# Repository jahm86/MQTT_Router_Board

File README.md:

# MQTT_Router_Board
Tarjeta electrónica para proyecto didáctico de router MQTT

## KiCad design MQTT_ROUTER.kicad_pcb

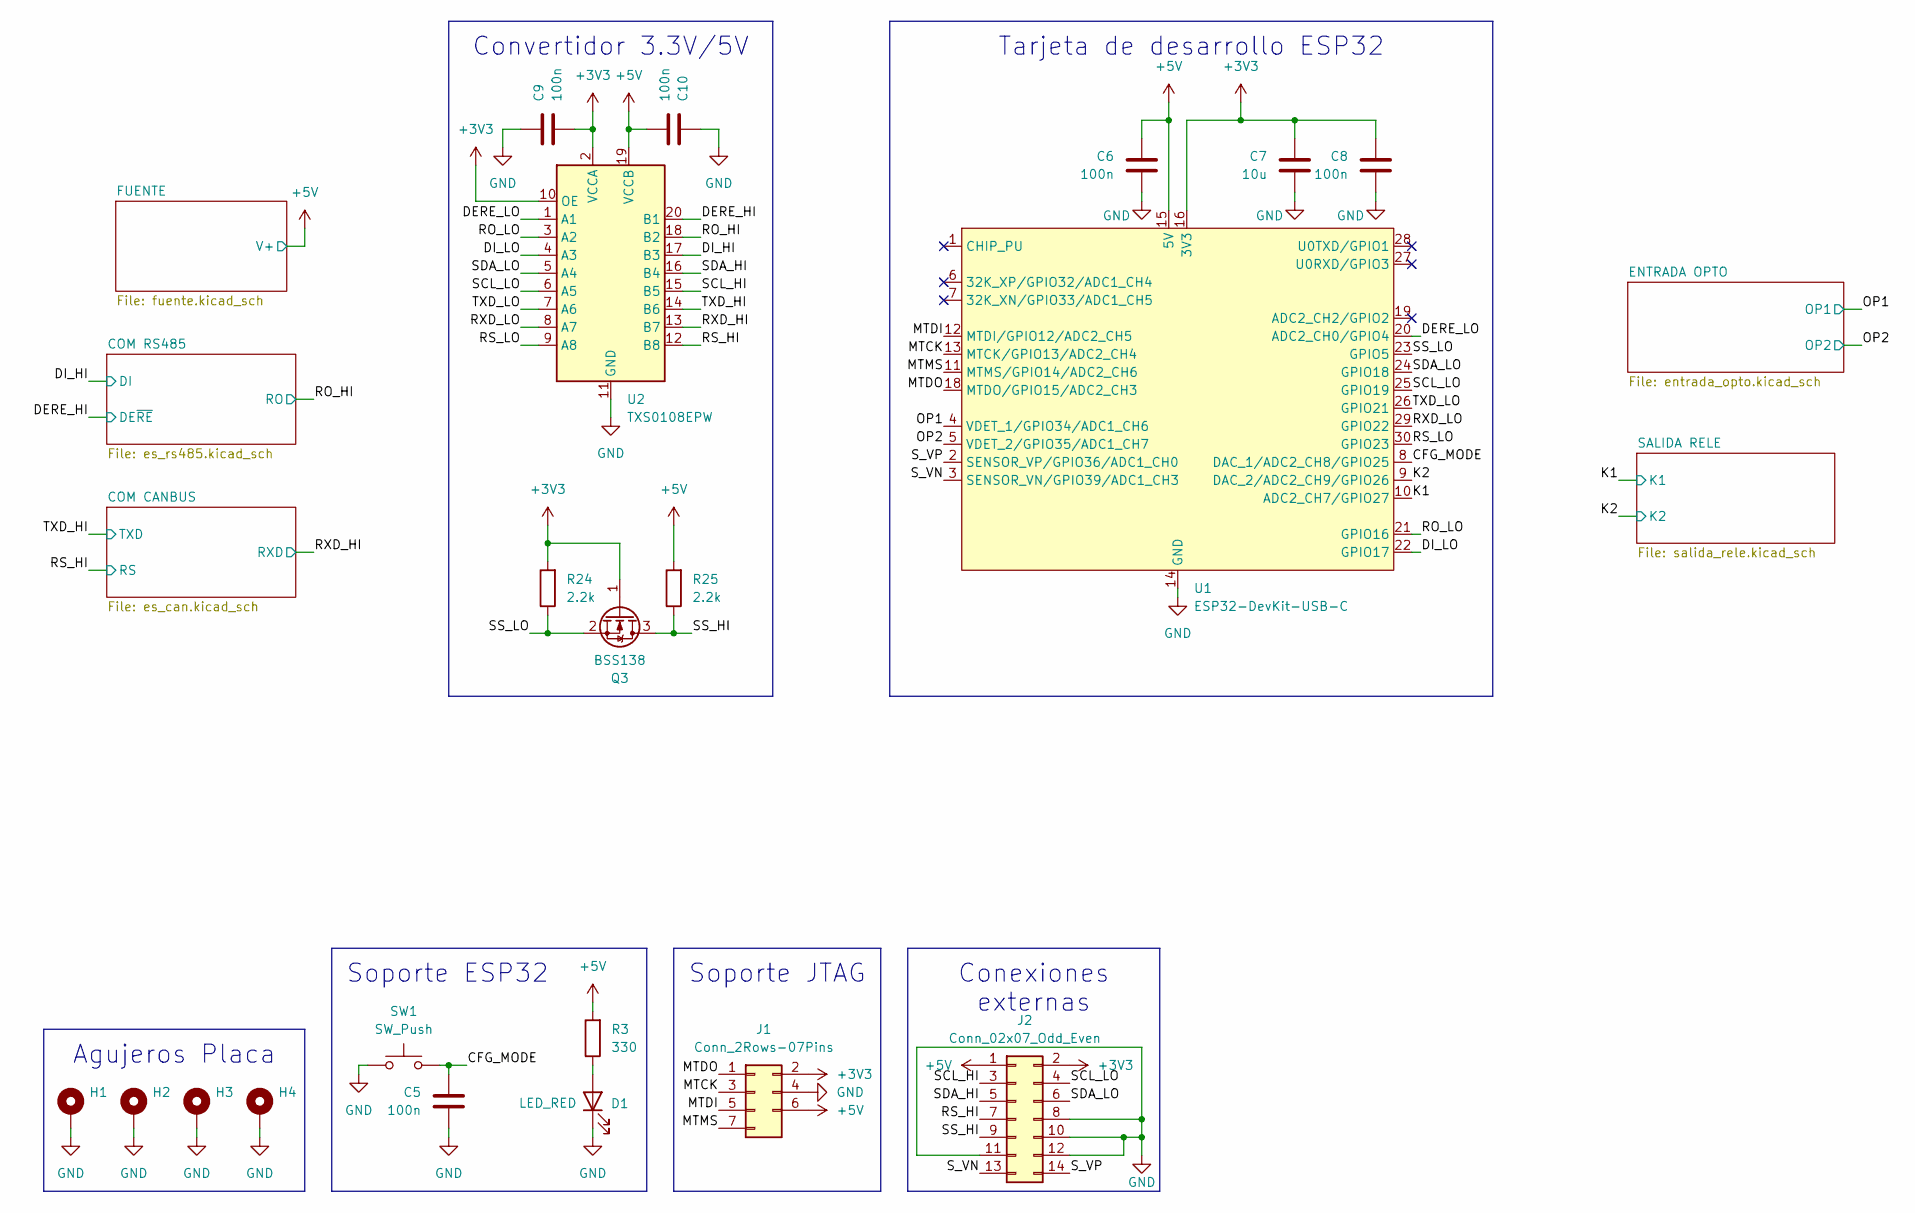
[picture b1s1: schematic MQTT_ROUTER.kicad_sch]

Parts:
C5, C6, C8, C9, C10: 100n; C_0805_2012Metric
C7: 10u; C_1206_3216Metric
D1: LED_RED; LED_D5.0mm
H1, H2, H3, H4: MountingHole_Pad; MountingHole_3.5mm_Pad_Via
J1: Conn_2Rows-07Pins; PinSocket_2x04_P2.54mm_Vertical
J2: Conn_02x07_Odd_Even; PinSocket_2x07_P2.54mm_Vertical
Q3: BSS138; SOT-23
R3: 330; R_0805_2012Metric
R24, R25: 2.2k; R_0805_2012Metric
SW1: SW_Push; SW_PUSH_6mm
U1: ESP32-DevKit-USB-C
U2: TXS0108EPW; TSSOP-20_4.4x6.5mm_P0.65mm

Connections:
+3V3: C7.1, C8.1, C9.2, J1.2, J2.2, Q3.1 (G), R24.2, U1.16 (3V3), U2.2 (VCCA), U2.10 (OE); also elsewhere on the board
+5V: C6.1, C10.2, J1.6, J2.1, R3.2, R25.2, U1.15 (5V), U2.19 (VCCB); also elsewhere on the board
/CFG_MODE: C5.1, SW1.2, U1.8 (DAC_1/ADC2_CH8/GPIO25)
/DERE_HI: U2.20 (B1); also elsewhere on the board
/DERE_LO: U1.20 (ADC2_CH0/GPIO4), U2.1 (A1)
/DI_HI: U2.17 (B3); also elsewhere on the board
/DI_LO: U1.22 (GPIO17), U2.4 (A3)
/K1: U1.10 (ADC2_CH7/GPIO27); also elsewhere on the board
/K2: U1.9 (DAC_2/ADC2_CH9/GPIO26); also elsewhere on the board
/MTCK: J1.3, U1.13 (MTCK/GPIO13/ADC2_CH4)
/MTDI: J1.5, U1.12 (MTDI/GPIO12/ADC2_CH5)
/MTDO: J1.1, U1.18 (MTDO/GPIO15/ADC2_CH3)
/MTMS: J1.7, U1.11 (MTMS/GPIO14/ADC2_CH6)
/OP1: U1.4 (VDET_1/GPIO34/ADC1_CH6); also elsewhere on the board
/OP2: U1.5 (VDET_2/GPIO35/ADC1_CH7); also elsewhere on the board
/RO_HI: U2.18 (B2); also elsewhere on the board
/RO_LO: U1.21 (GPIO16), U2.3 (A2)
/RS_HI: J2.7, U2.12 (B8); also elsewhere on the board
/RS_LO: U1.30 (GPIO23), U2.9 (A8)
/RXD_HI: U2.13 (B7); also elsewhere on the board
/RXD_LO: U1.29 (GPIO22), U2.8 (A7)
/SCL_HI: J2.3, U2.15 (B5)
/SCL_LO: J2.4, U1.25 (GPIO19), U2.6 (A5)
/SDA_HI: J2.5, U2.16 (B4)
/SDA_LO: J2.6, U1.24 (GPIO18), U2.5 (A4)
/SS_HI: J2.9, Q3.3 (D), R25.1
/SS_LO: Q3.2 (S), R24.1, U1.23 (GPIO5)
/S_VN: J2.13, U1.3 (SENSOR_VN/GPIO39/ADC1_CH3)
/S_VP: J2.14, U1.2 (SENSOR_VP/GPIO36/ADC1_CH0)
/TXD_HI: U2.14 (B6); also elsewhere on the board
/TXD_LO: U1.26 (GPIO21), U2.7 (A6)
GND: C5.2, C6.2, C7.2, C8.2, C9.1, C10.1, D1.1 (K), H1.1, H2.1, H3.1, H4.1, J1.4, J2.8, J2.10, J2.11, J2.12, SW1.1, U1.14 (GND), U1.17 (GND), U2.11 (GND); also elsewhere on the board
unnamed: D1.2 (A), R3.1

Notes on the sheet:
Soporte ESP32
Agujeros Placa
Convertidor 3.3V/5V
Tarjeta de desarrollo ESP32
Soporte JTAG
Conexiones externas

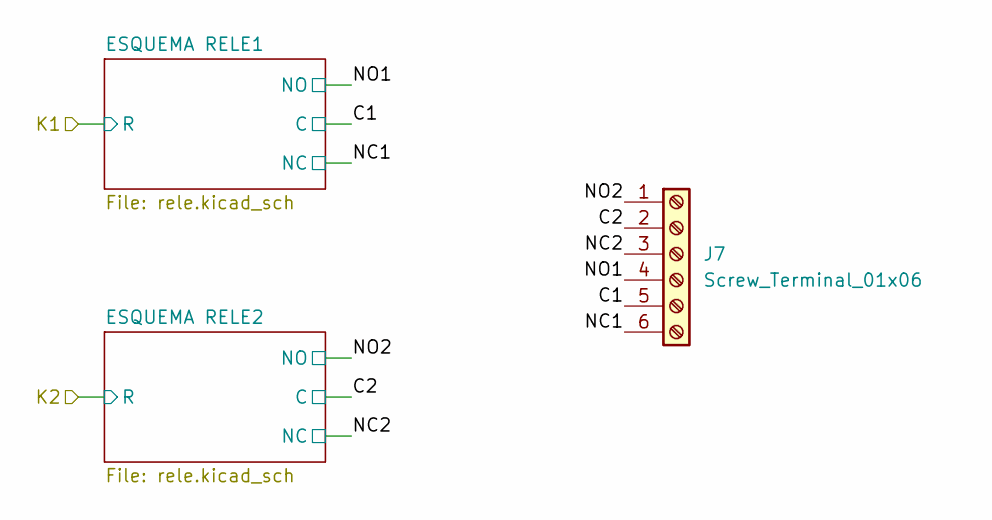
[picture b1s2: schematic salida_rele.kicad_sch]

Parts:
J7: Screw_Terminal_01x06; TerminalBlock_Phoenix_MKDS-1,5-6_1x06_P5.00mm_Horizontal

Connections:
/SALIDA RELE/C1: J7.5; also elsewhere on the board
/SALIDA RELE/C2: J7.2; also elsewhere on the board
/SALIDA RELE/NC1: J7.6; also elsewhere on the board
/SALIDA RELE/NC2: J7.3; also elsewhere on the board
/SALIDA RELE/NO1: J7.4; also elsewhere on the board
/SALIDA RELE/NO2: J7.1; also elsewhere on the board

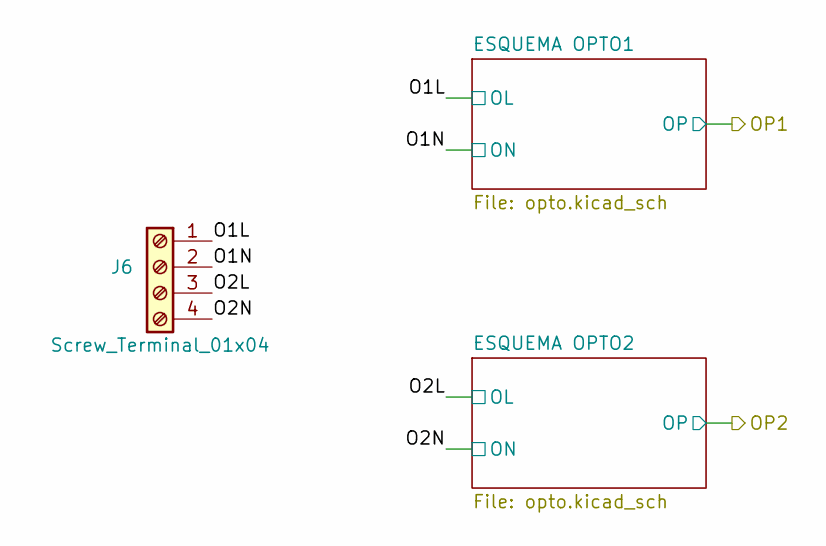
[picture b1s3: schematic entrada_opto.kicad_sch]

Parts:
J6: Screw_Terminal_01x04; TerminalBlock_Phoenix_MKDS-1,5-4_1x04_P5.00mm_Horizontal

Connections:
/ENTRADA OPTO/O1L: J6.1; also elsewhere on the board
/ENTRADA OPTO/O1N: J6.2; also elsewhere on the board
/ENTRADA OPTO/O2L: J6.3; also elsewhere on the board
/ENTRADA OPTO/O2N: J6.4; also elsewhere on the board

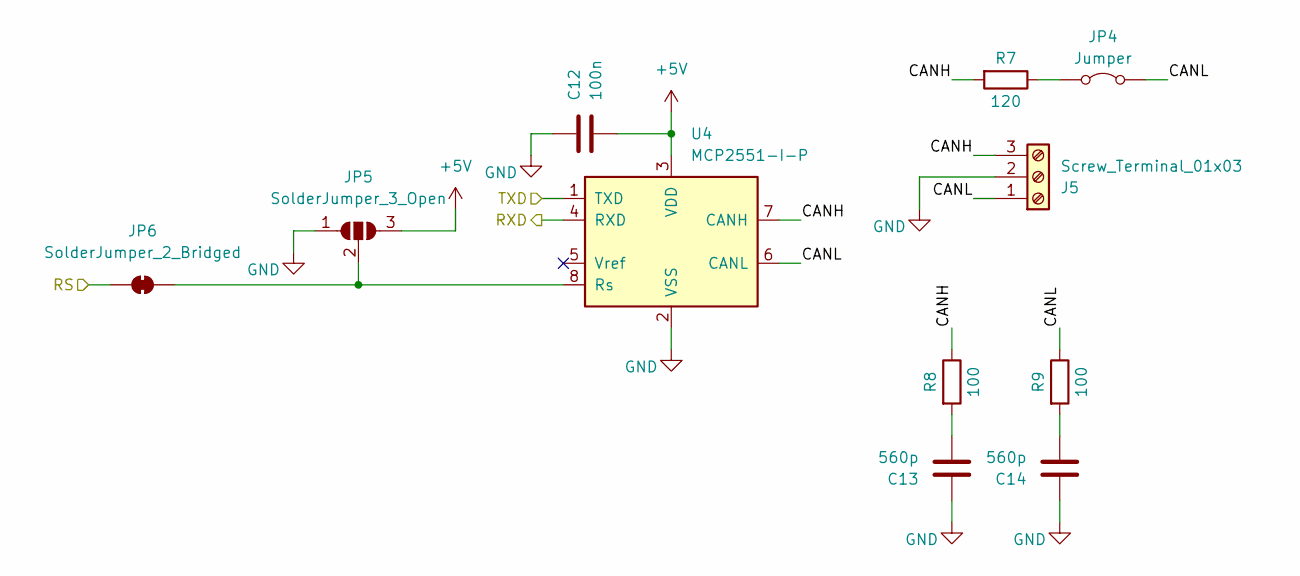
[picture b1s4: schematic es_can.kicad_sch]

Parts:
C12: 100n; C_0805_2012Metric
C13, C14: 560p; C_0805_2012Metric
J5: Screw_Terminal_01x03; TerminalBlock_Phoenix_MKDS-1,5-3_1x03_P5.00mm_Horizontal
JP4: Jumper; PinHeader_1x02_P2.54mm_Vertical
JP5: SolderJumper_3_Open; SolderJumper-3_P1.3mm_Open_RoundedPad1.0x1.5mm
JP6: SolderJumper_2_Bridged; SolderJumper-2_P1.3mm_Bridged_RoundedPad1.0x1.5mm
R7: 120; R_0805_2012Metric
R8, R9: 100; R_0805_2012Metric
U4: MCP2551-I-P; DIP-8_W7.62mm

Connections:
+5V: C12.2, JP5.3 (B), U4.3 (VDD); also elsewhere on the board
/COM CANBUS/CANH: J5.3, R7.2, R8.1, U4.7 (CANH)
/COM CANBUS/CANL: J5.1, JP4.2 (B), R9.1, U4.6 (CANL)
/RS_HI: JP6.1 (A); also elsewhere on the board
/RXD_HI: U4.4 (RXD); also elsewhere on the board
/TXD_HI: U4.1 (TXD); also elsewhere on the board
GND: C12.1, C13.1, C14.1, J5.2, JP5.1 (A), U4.2 (VSS); also elsewhere on the board
unnamed: C13.2, R8.2
unnamed: C14.2, R9.2
unnamed: JP4.1 (A), R7.1
unnamed: JP5.2 (C), JP6.2 (B), U4.8 (Rs)

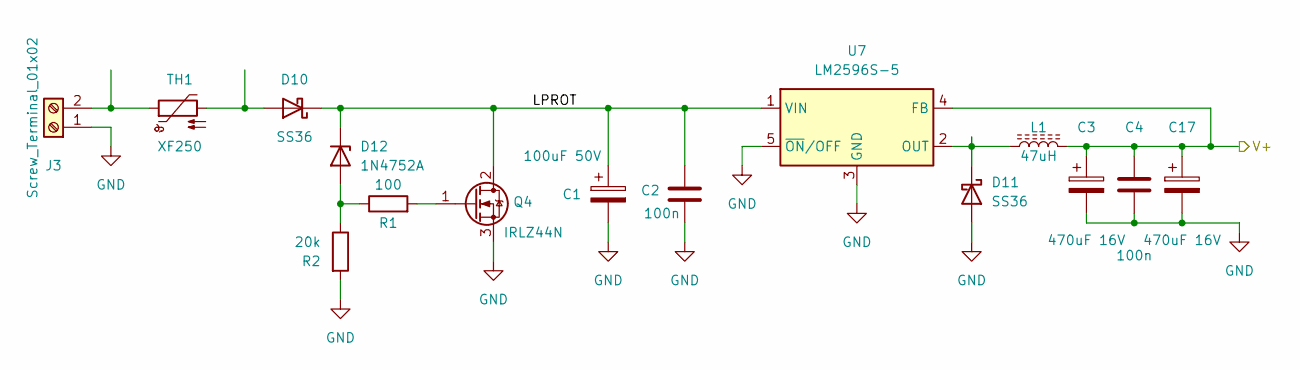
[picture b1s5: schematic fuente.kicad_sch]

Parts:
C1: 100uF 50V; CP_Radial_D10.0mm_P5.00mm
C2, C4: 100n; C_0805_2012Metric
C3, C17: 470uF 16V; CP_Radial_D10.0mm_P5.00mm
D10, D11: SS36; D_SMC
D12: 1N4752A; D_DO-41_SOD81_P10.16mm_Horizontal
J3: Screw_Terminal_01x02; TerminalBlock_Phoenix_MKDS-1,5-2_1x02_P5.00mm_Horizontal
L1: 47uH; L_Bourns_SRR1260
Q4: IRLZ44N; TO-220-3_Horizontal_TabDown
R1: 100; R_0805_2012Metric
R2: 20k; R_0805_2012Metric
TH1: XF250; Fuse_BelFuse_0ZRE0125FF_L21.2mm_W5.3mm
U7: LM2596S-5; TO-263-5_TabPin3

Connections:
+5V: C3.1, C4.1, C17.1, L1.2, U7.4 (FB); also elsewhere on the board
/FUENTE/LPROT: C1.1, C2.1, D10.1 (K), D12.1 (K), Q4.2 (D), U7.1 (VIN)
GND: C1.2, C2.2, C3.2, C4.2, C17.2, D11.2 (A), J3.1, Q4.3 (S), R2.2, U7.3 (GND), U7.5 (~ON/OFF); also elsewhere on the board
unnamed: D10.2 (A), TH1.2
unnamed: D11.1 (K), L1.1, U7.2 (OUT)
unnamed: D12.2 (A), R1.1, R2.1
unnamed: J3.2, TH1.1
unnamed: Q4.1 (G), R1.2

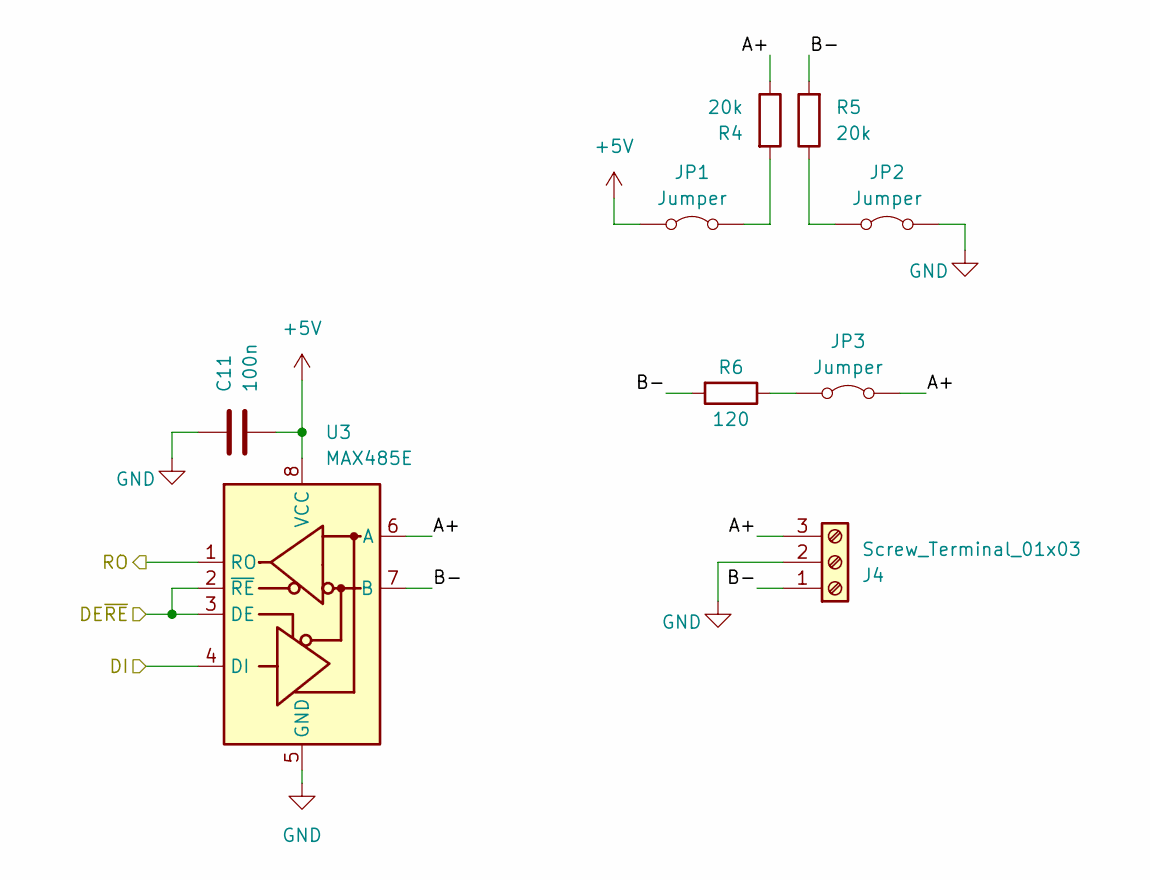
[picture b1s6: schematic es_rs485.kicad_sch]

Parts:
C11: 100n; C_0805_2012Metric
J4: Screw_Terminal_01x03; TerminalBlock_Phoenix_MKDS-1,5-3_1x03_P5.00mm_Horizontal
JP1, JP2, JP3: Jumper; PinHeader_1x02_P2.54mm_Vertical
R4, R5: 20k; R_0805_2012Metric
R6: 120; R_0805_2012Metric
U3: MAX485E; SOIC-8_3.9x4.9mm_P1.27mm

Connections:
+5V: C11.2, JP1.1 (A), U3.8 (VCC); also elsewhere on the board
/COM RS485/A+: J4.3, JP3.2 (B), R4.1, U3.6 (A)
/COM RS485/B-: J4.1, R5.2, R6.2, U3.7 (B)
/DERE_HI: U3.2 (~RE), U3.3 (DE); also elsewhere on the board
/DI_HI: U3.4 (DI); also elsewhere on the board
/RO_HI: U3.1 (RO); also elsewhere on the board
GND: C11.1, J4.2, JP2.1 (A), U3.5 (GND); also elsewhere on the board
unnamed: JP1.2 (B), R4.2
unnamed: JP2.2 (B), R5.1
unnamed: JP3.1 (A), R6.1

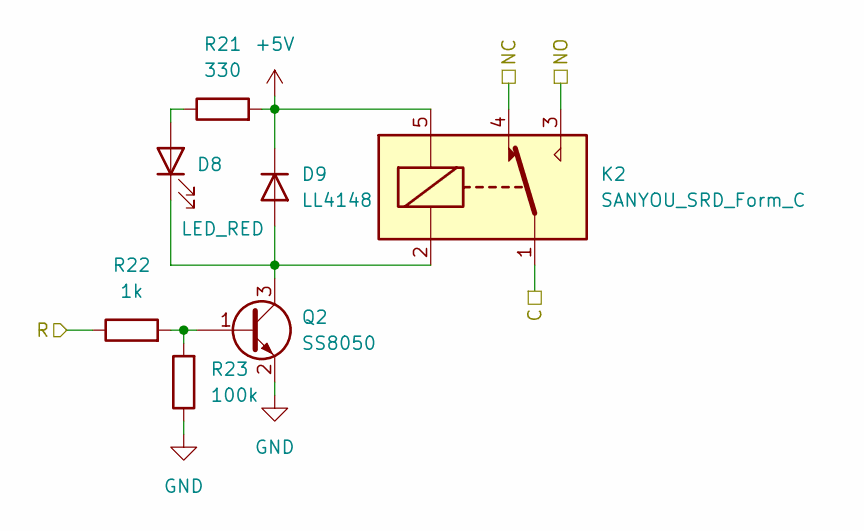
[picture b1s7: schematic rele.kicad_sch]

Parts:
D8: LED_RED; LED_D5.0mm
D9: LL4148; D_MiniMELF
K2: SANYOU_SRD_Form_C; Relay_SPDT_SANYOU_SRD_Series_Form_C
Q2: SS8050; SOT-23
R21: 330; R_0805_2012Metric
R22: 1k; R_0805_2012Metric
R23: 100k; R_0805_2012Metric

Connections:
+5V: D9.1 (K), K2.5, R21.2; also elsewhere on the board
/K2: R22.1; also elsewhere on the board
/SALIDA RELE/C2: K2.1; also elsewhere on the board
/SALIDA RELE/NC2: K2.4; also elsewhere on the board
/SALIDA RELE/NO2: K2.3; also elsewhere on the board
GND: Q2.2 (E), R23.1; also elsewhere on the board
unnamed: D8.2 (A), R21.1
unnamed: D8.1 (K), D9.2 (A), K2.2, Q2.3 (C)
unnamed: Q2.1 (B), R22.2, R23.2

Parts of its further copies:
D6: LED_RED; LED_D5.0mm
D7: LL4148; D_MiniMELF
K1: SANYOU_SRD_Form_C; Relay_SPDT_SANYOU_SRD_Series_Form_C
Q1: SS8050; SOT-23
R18: 330; R_0805_2012Metric
R19: 1k; R_0805_2012Metric
R20: 100k; R_0805_2012Metric

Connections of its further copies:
+5V: D7.1 (K), K1.5, R18.2; also elsewhere on the board
/K1: R19.1; also elsewhere on the board
/SALIDA RELE/C1: K1.1; also elsewhere on the board
/SALIDA RELE/NC1: K1.4; also elsewhere on the board
/SALIDA RELE/NO1: K1.3; also elsewhere on the board
GND: Q1.2 (E), R20.1; also elsewhere on the board
unnamed: D6.2 (A), R18.1
unnamed: D6.1 (K), D7.2 (A), K1.2, Q1.3 (C)
unnamed: Q1.1 (B), R19.2, R20.2

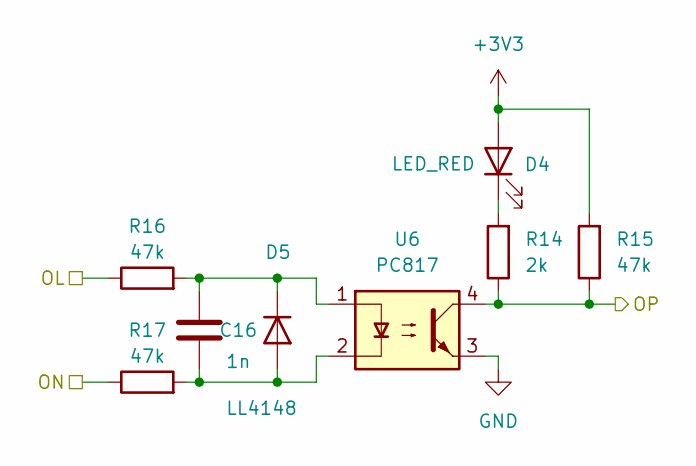
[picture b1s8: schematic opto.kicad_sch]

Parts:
C16: 1n; C_0805_2012Metric
D4: LED_RED; LED_D5.0mm
D5: LL4148; D_MiniMELF
R14: 2k; R_0805_2012Metric
R15: 47k; R_0805_2012Metric
R16, R17: 47k; R_1206_3216Metric
U6: PC817; DIP-4_W7.62mm

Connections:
+3V3: D4.2 (A), R15.2; also elsewhere on the board
/ENTRADA OPTO/O2L: R16.1; also elsewhere on the board
/ENTRADA OPTO/O2N: R17.1; also elsewhere on the board
/OP2: R14.1, R15.1, U6.4; also elsewhere on the board
GND: U6.3; also elsewhere on the board
unnamed: D4.1 (K), R14.2
unnamed: C16.2, D5.2 (A), R17.2, U6.2
unnamed: C16.1, D5.1 (K), R16.2, U6.1

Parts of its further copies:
C15: 1n; C_0805_2012Metric
D2: LED_RED; LED_D5.0mm
D3: LL4148; D_MiniMELF
R10: 2k; R_0805_2012Metric
R11: 47k; R_0805_2012Metric
R12, R13: 47k; R_1206_3216Metric
U5: PC817; DIP-4_W7.62mm

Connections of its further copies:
+3V3: D2.2 (A), R11.2; also elsewhere on the board
/ENTRADA OPTO/O1L: R12.1; also elsewhere on the board
/ENTRADA OPTO/O1N: R13.1; also elsewhere on the board
/OP1: R10.1, R11.1, U5.4; also elsewhere on the board
GND: U5.3; also elsewhere on the board
unnamed: D2.1 (K), R10.2
unnamed: C15.2, D3.2 (A), R13.2, U5.2
unnamed: C15.1, D3.1 (K), R12.2, U5.1

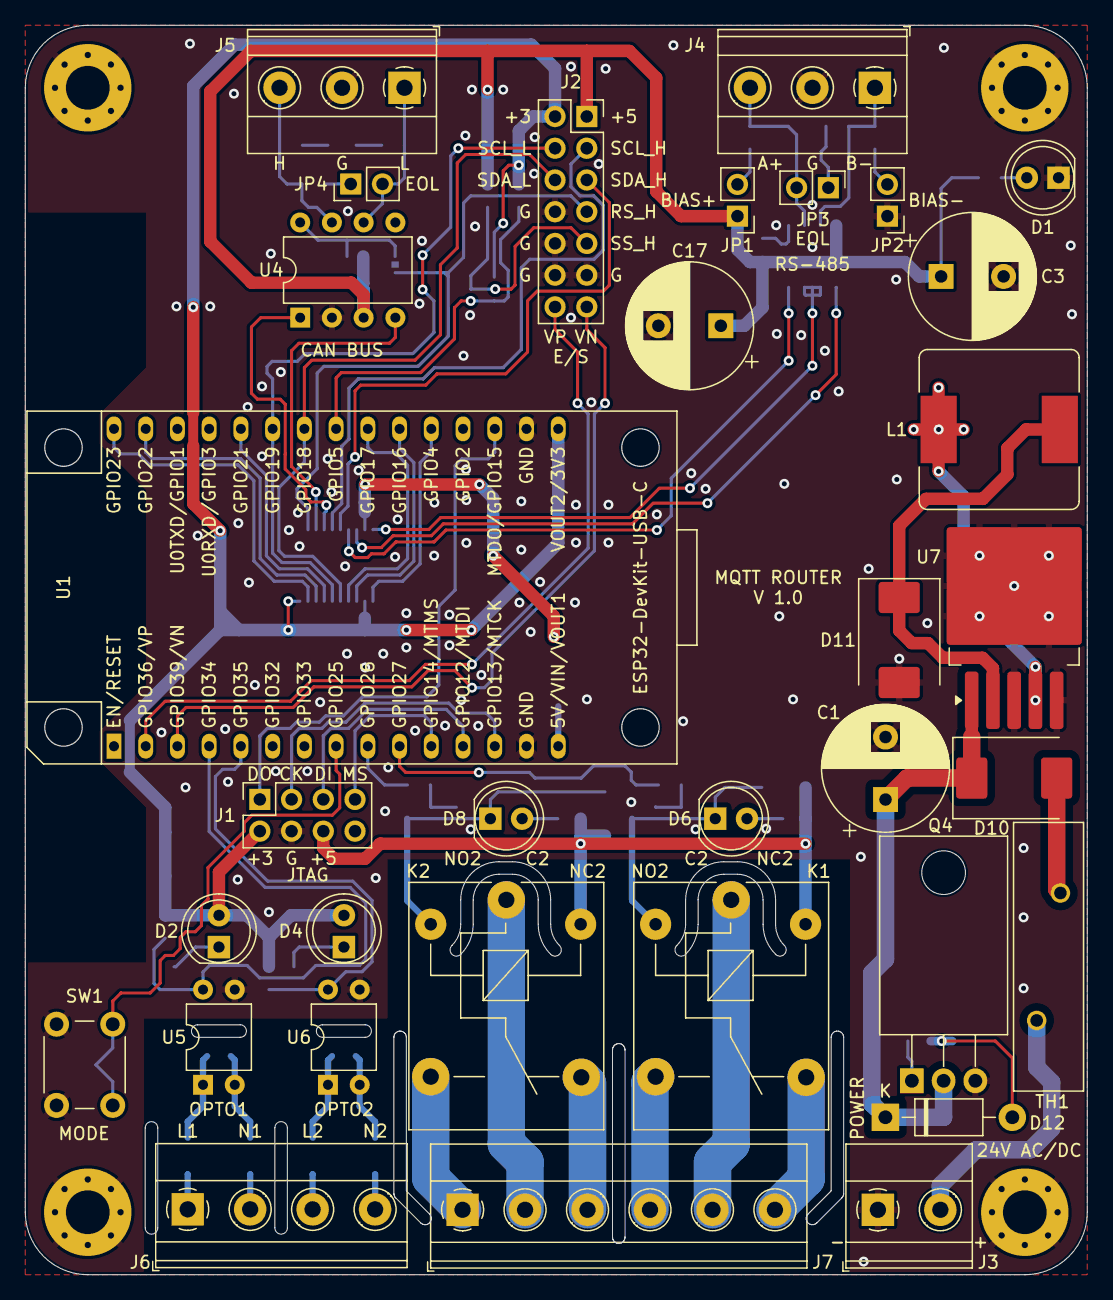
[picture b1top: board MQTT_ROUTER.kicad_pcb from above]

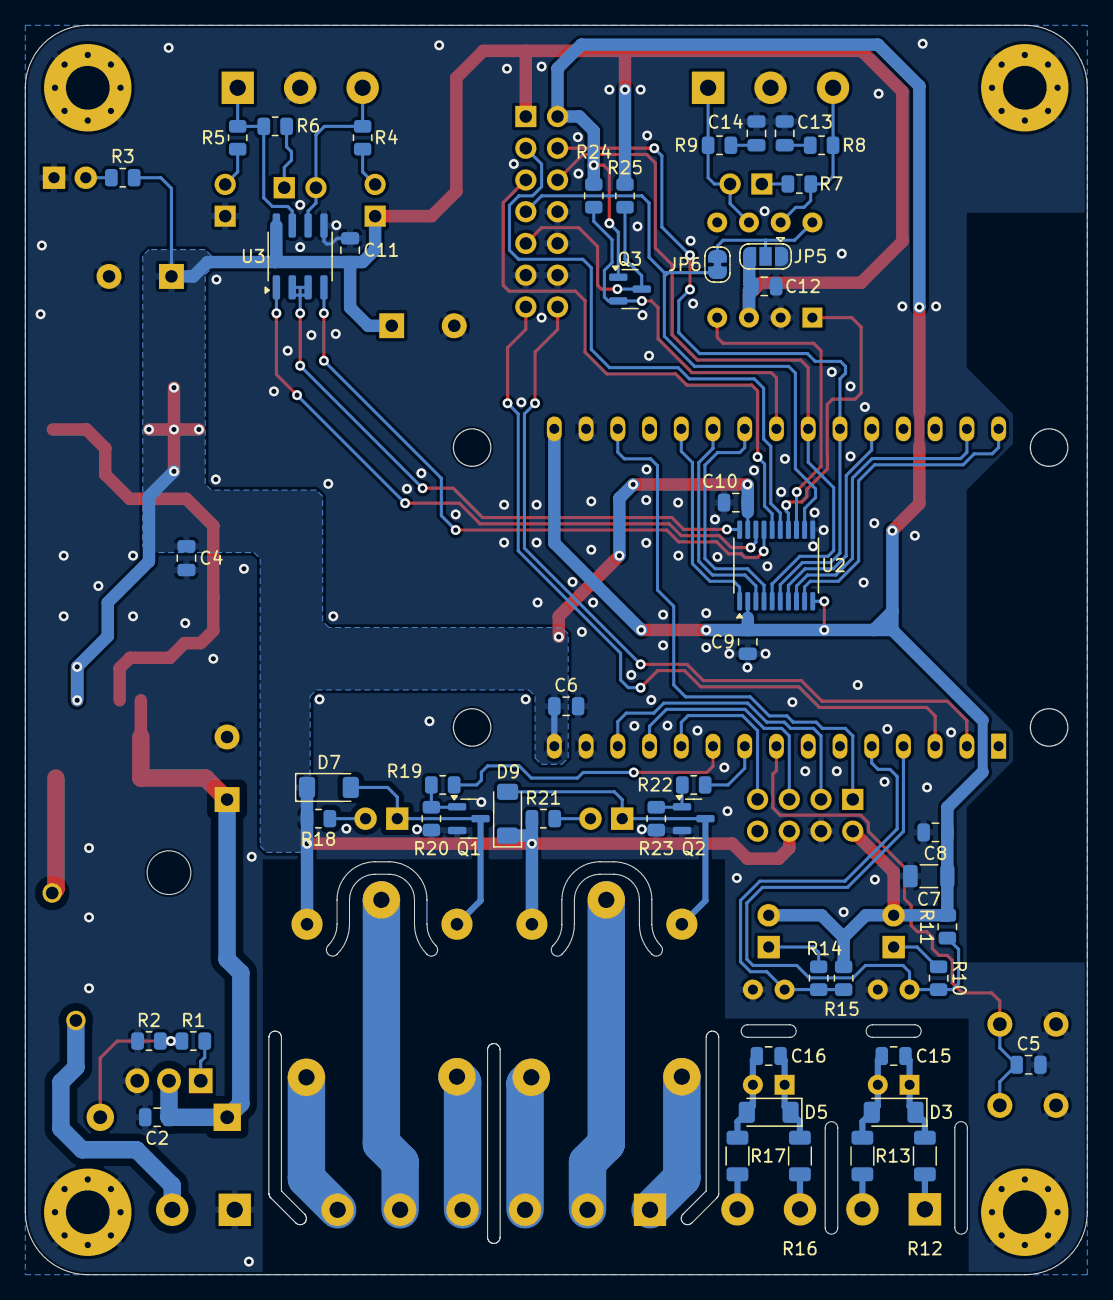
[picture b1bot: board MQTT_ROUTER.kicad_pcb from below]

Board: 2 copper layers, 85.0 x 99.9 mm, 87 parts (50 on the bottom side), 72 nets.

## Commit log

2025-10-14 Primera encomienda
2025-10-17 Reparar ubicación de serigrafías y errores de DRC. Mejorar pistas de 5V y 3V.
2025-10-26 Agregar nueva tarjeta ESP32 USB-C, con repo creado recientemente
2025-10-28 Actualizar componentes, pistas e imágenes
2026-01-02 Agregar protección de sobre tensión/tensión inversa
2026-01-02 Agregar protección de sobre tensión/tensión inversa (2)
2026-01-02 Agregar protección de sobre tensión/tensión inversa (3)
2026-01-02 Agregar protección de sobre tensión/tensión inversa (4)
2026-01-02 Cambiar agujeros de placa, invertir terminales de fuente
2026-01-03 Actualizar PCB
2026-01-03 Actualizar imagenes
2026-01-03 Actualizar zener a 1N4752A (33V)
2026-01-07 Ajustar grosor de pistas S_VP/S_VN
2026-01-07 Aumentar mínimo de vía a 0.8/0.4
2026-01-07 Aumentar mínimo de vía a 0.8/0.4 (2)
2026-01-11 Actualizar PCB (2)
2026-01-11 Actualizar PCB (3)
2026-01-11 Aumentar distancia entre soldermask y pad en PCB
2026-01-13 Corregir distancia entre soldermask y pad en PCB
2026-02-03 Agregar más ranuras de aislamiento
